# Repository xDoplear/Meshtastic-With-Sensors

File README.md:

The included Arduino Program is designed for a Adafruit Trinket M0. If you want to use a different microcontroller, you may have to modify the code. KiCAD files for the project, schematic, and PCB are included.

# Meshtastic Heltec Sensor Config For Meshtastic App
1. Connect to the Meshtastic Radio that you want to configure. For any config import/modification, the Meshtastic device will have to restart before the config is set.
2. Press three dots on top right corner
3. Go to "Radio configuration"
4. Scroll down until you see "Import configuration" and press it
5. Import the config file named "All Sensor Final Config". This is the current configuration of the current sensor Heltecs.
   There is one called "All Sensor Final Cong" as well. This should also work but I just made a typo.
6. Go back to the "Radio configuration" and find the "Power" tab. This is where you can enable/disable power saving mode. This should be disabled in the imported configuration.
7. Under the "User" tab, change the name of the device to a fitting name. Ex: All Sensor 4
8. If you want to double check if the configuration is right or if you do not have access to the file, the following are the important settings that need to be changed
   - On the main screen, go to the gear tab on the right and make sure your region is US. You can also change your name here as well.
   - On the channels tab (the circle with a sideways wifi Logo), there should be a place to enter a URL. Enter the following URL:
     https://meshtastic.org/e/#CjESIJX6cYPXaTCkQ90MgZlJb7ExMa7bxA76L3uKXQBcwBAvGglNZW5kZXpMYWI6AgggEgwIATgBQANIAVAeaAE 
     The name of the private channel should be "MendezLab"
   - The following settings will be under "Radio configuration" section
     - Go to "Device" and change the role to CLIENT_HIDDEN and enable Serial output
     - Go to "Power" and do the following. **These values may need tinkering**
         - Enable Power Saving Mode (if you see fit)
         - Change the wait for bluetooth setting to 30 seconds
         - Change both super deep sleep and light sleep duration to 300 seconds
         - Change minimum wake time to 10 seconds
      - Go to "Display" and change screen timeout to 5 seconds
      - Go to "Bluetooth" and enable bluetooth (this should already be enabled)
     - Under the "Module Configuration" go to "Serial" and do the following
         - Enable Serial
         - Enable Echo (optional)
         - Change RX pin to 18 and TX pin to 17 (change as needed, just make sure selected pins are actually UART pins or else an error will occur)
         - Change Baud rate to 9600 (this can be changed if needed, just make sure to do so in the Arduino code as well)
         - Set timeout to 1
         - Change the "Serial mode" setting to TEXTMSG

  For the Sensor Receiver Heltec, you can import the same "All Sensor Final Config" file but change the following settings:
  1. Under "Device", change role to CLIENT_MUTE
  2. Under "Serial", change baud rate to 115200

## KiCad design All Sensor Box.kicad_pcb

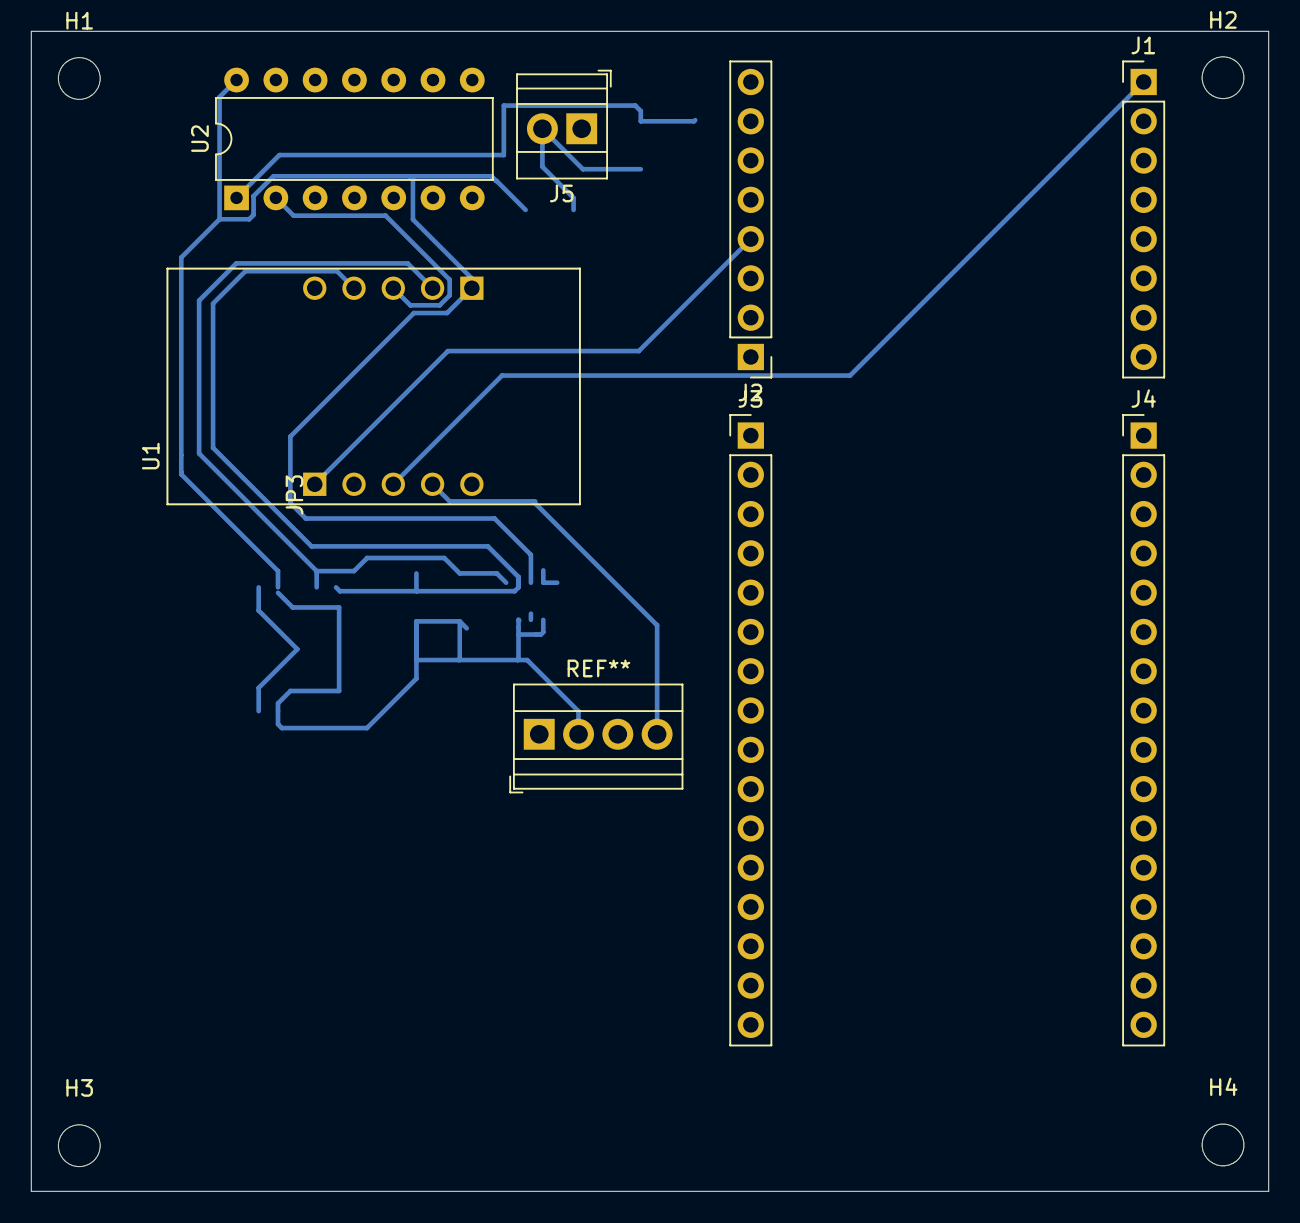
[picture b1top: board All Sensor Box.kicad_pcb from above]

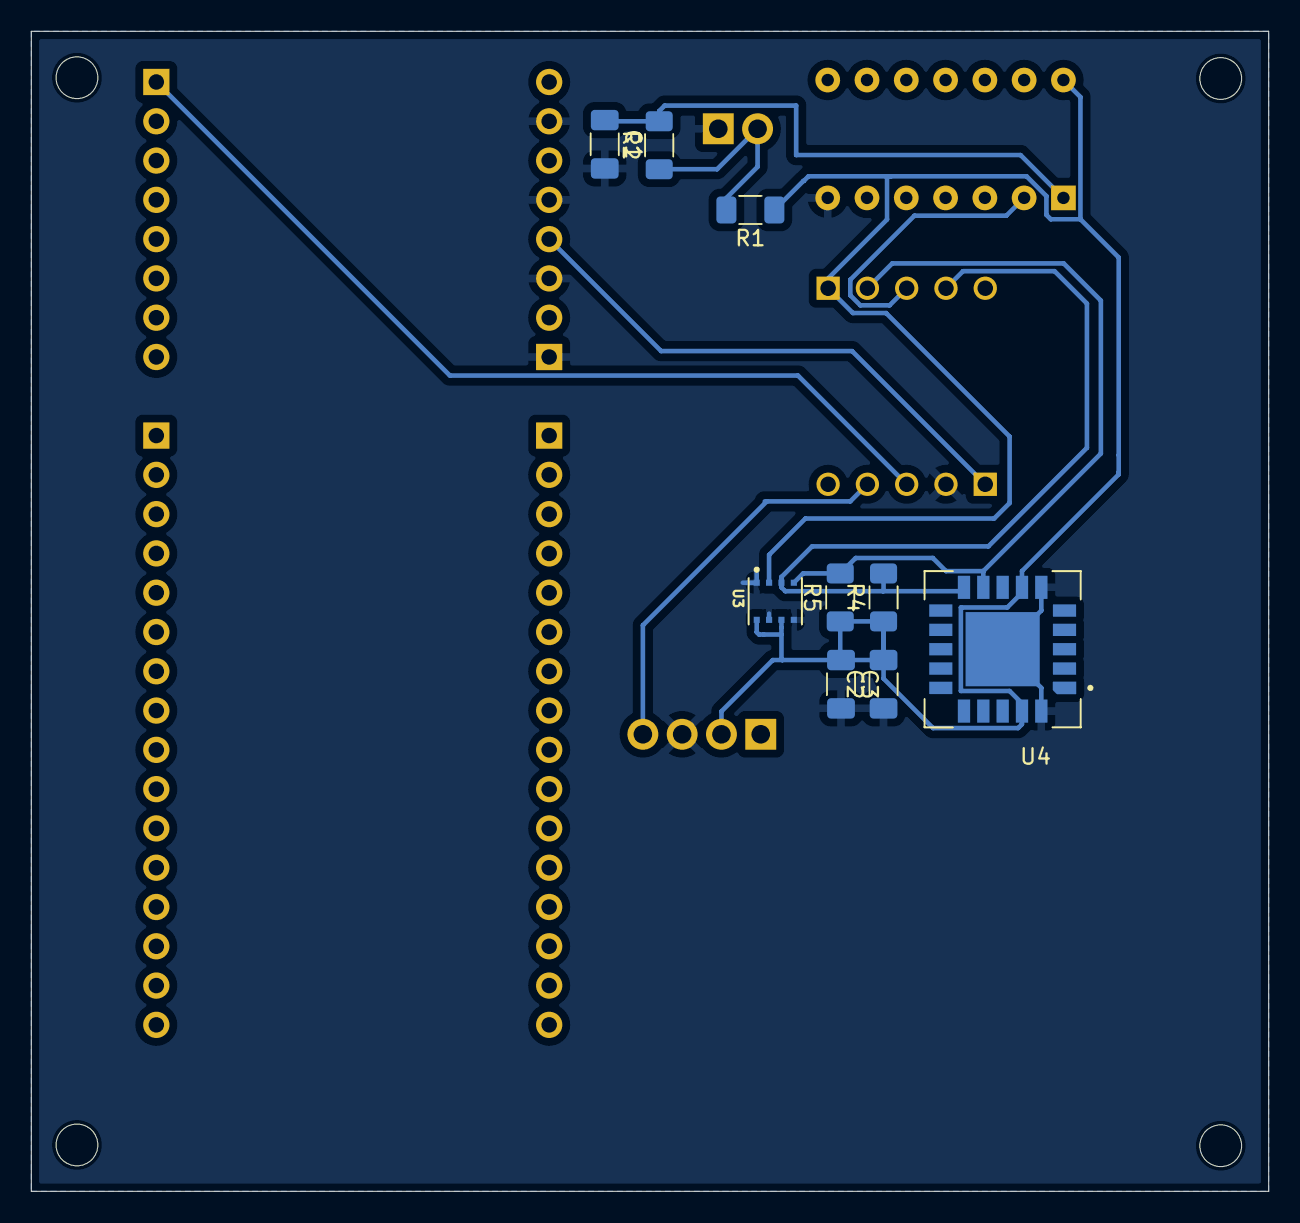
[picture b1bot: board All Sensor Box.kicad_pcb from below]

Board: 2 copper layers, 80.0 x 75.0 mm, 20 parts (9 on the bottom side), 9 nets.

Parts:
C1: 10uF; C_1206_3216Metric_Pad1.33x1.80mm_HandSolder
C2, C3: 100nF; C_1206_3216Metric_Pad1.33x1.80mm_HandSolder
H1, H2, H3, H4: MountingHole; MountingHole_2.7mm
J1: Conn_01x08_Pin; PinHeader_1x08_P2.54mm_Vertical
J2: Heltec Wireless Tracker v1.1; PinHeader_1x08_P2.54mm_Vertical
J3, J4: Conn_01x16_Pin; PinHeader_1x16_P2.54mm_Vertical
J5: Screw_Terminal_01x02; TerminalBlock_Xinya_XY308-2.54-2P_1x02_P2.54mm_Horizontal
R1: 10k; R_1206_3216Metric_Pad1.30x1.75mm_HandSolder
R2: 100; R_1206_3216Metric_Pad1.30x1.75mm_HandSolder
R4, R5: 4.7k; R_1206_3216Metric_Pad1.30x1.75mm_HandSolder
U1: 3500; MODULE_3500
U2: 74HC14; DIP-14_W7.62mm
U3: BME688; IC_BME688
U4: SCD41-D-R2; XDCR_SCD41-D-R2

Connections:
/3V3: C2.2, C3.1, R1.1, R4.1, R5.1, U1.JP4_1 (3.3V), U3.2 (CSB), U3.6 (VDDIO), U3.8 (VDD), U4.7 (VDD), U4.19 (VDDH)
/Bat: J2.4, U1.JP3_1 (VBAT)
/RAIN: U1.JP4_3 (D1_A0_PA02), U2.2
/RX: J1.RX (Pin_1), U1.TX (D4_A2_PA06_TXD_MOSI)
/SCL: R5.2, U1.JP4_2 (D2_A1_PA09_SCL_MISO), U3.4 (SCK), U4.9 (SCL)
/SDA: R4.2, U1.JP4_4 (D0_A4_PA08_SDA), U3.3 (SDI), U4.10 (SDA)
/SW_Power: J5.2, R1.2, R2.1
GND: C1.2, C2.1, C3.2, J2.1, J2.3, J2.5, J2.7, J5.1, U1.JP3_2 (GND), U2.7, U3.1 (GND), U3.5 (SDO), U3.7 (GND), U4.6 (GND), U4.20 (GND), U4.21 (GND)
unnamed: C1.1, R2.2, U2.1

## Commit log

2024-08-21 Add files via upload
    Final Arduino Code to send data from BME688 and SCD41 through serial. Code is made for Adafruit Trinket M0 but can be modified for other boards as well.
2024-08-21 Add files via upload
    Project, Schematic, and PCB files for Adafruit Trinket M0, Heltec Tracker v1.1, BME688, SCD41, circuit for rain gauge, and connections for geophone.
2024-08-21 Add files via upload
    All Schematic and PCB related files for Heltec Tracker V1.1, Adafruit Trinket M0, and other sensors involved.
2024-08-23 Meshtastic Radio Config.md
    Instructions for how to configure the Meshtastic Devices for the current configuration
